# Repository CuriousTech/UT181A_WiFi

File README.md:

# UT181A_WiFi
Uni-T UT181A WiFi Interface  

Optically isolated interface for the UT181A using the ESP8266 for WiFi in either STA or AP mode. USB Rechargeable 1 cell LiPo and optional OLED display, which should be disabled for speed.  

The code is complete. There should be more export formats though. There's a basic web interface and binary WebSocket for a Windows software interface.  
[WindowsApp](https://www.curioustech.net/ut181a.html)  

Web page.  Click the white time on top to update the internal clock. The rest should be the same as what's on the DMM. 

File manager.  Click Saves or Records for listings. Click on files to download, and X to delete.

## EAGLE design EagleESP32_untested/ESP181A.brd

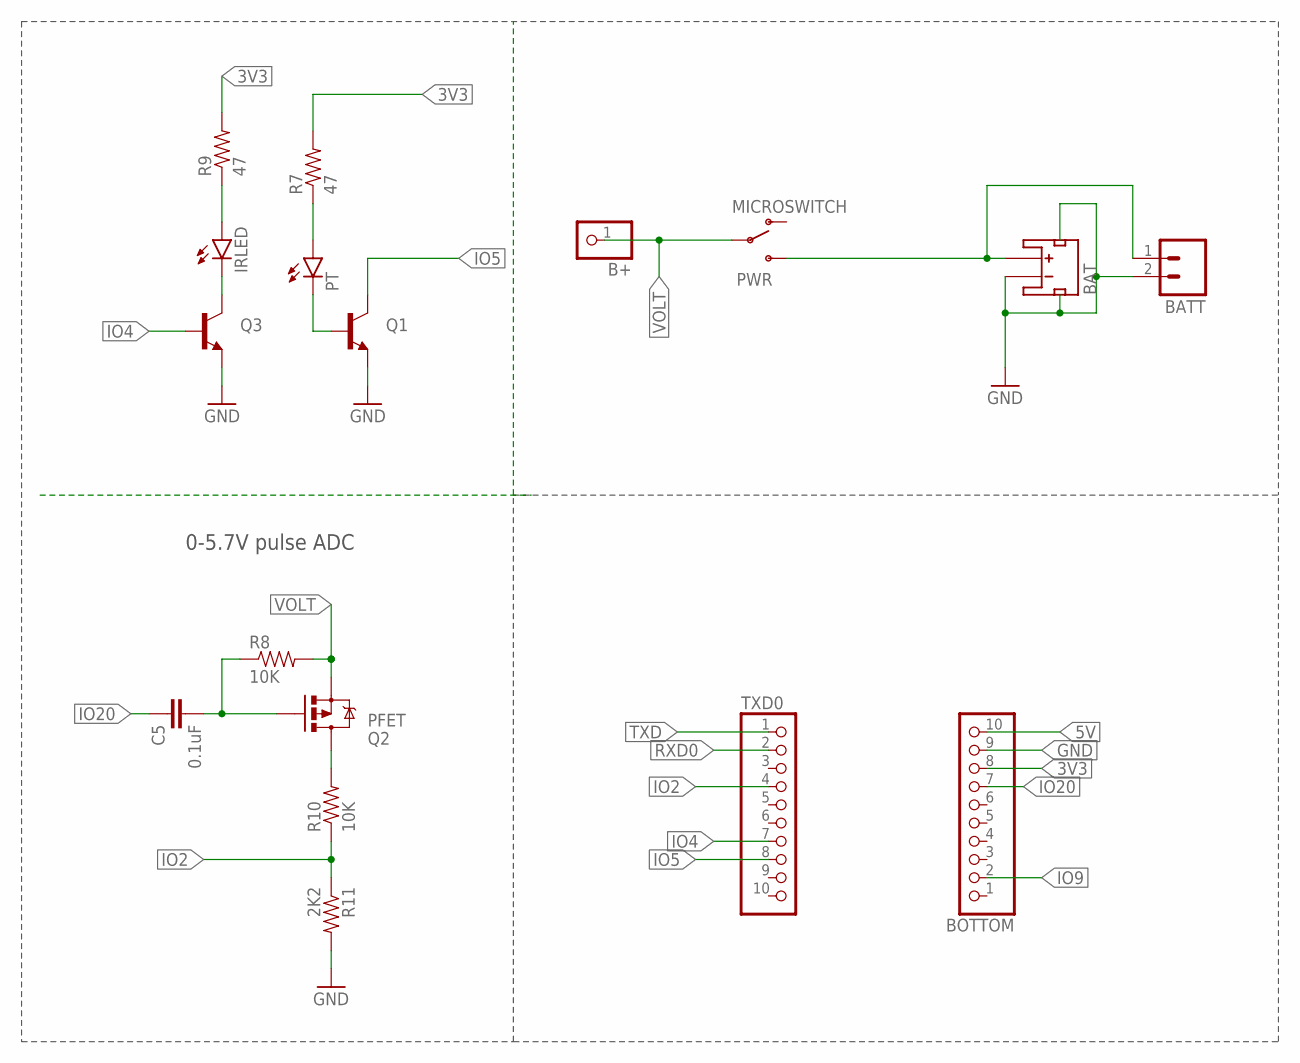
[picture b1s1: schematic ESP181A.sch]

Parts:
B+: PINHD-1X1; 1X01
BAT: JST1.25MM; JST_1.25MM
BATT: M02PTH; 1X02
BOTTOM: PINHD-1X10; 1X10
C5: 0.1uF; 0805-CAP
IRLED: LED3MM
PT: LED3MM
PWR: MICROSWITCH
Q1, Q3: TRANSISTOR_NPNSOT23-3; SOT23-3
Q2: PFET; SOT23-3
R7, R9: 47; 0805
R8, R10: 10K; 0805
R11: 2K2; 0805
TXD0: PINHD-1X10; 1X10

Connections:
3V3: BOTTOM.8, R7.2, R9.2
5V: BOTTOM.10
GND: BAT.1 (-), BAT.NC1 (PAD1), BAT.NC2 (PAD2), BATT.2, BOTTOM.9, Q1.2 (E), Q3.2 (E), R11.2
IO2: R10.1, R11.1, TXD0.4
IO4: Q3.1 (B), TXD0.7
IO5: Q1.3 (C), TXD0.8
IO9: BOTTOM.2
IO20: BOTTOM.7, C5.1
unnamed: IRLED.A, R9.1
unnamed: PT.K (C), Q1.1 (B)
unnamed: BAT.2 (+), BATT.1, PWR.3 (S)
unnamed: PT.A, R7.1
unnamed: C5.2, Q2.1 (G), R8.1
unnamed: Q2.3 (D), R10.2
unnamed: IRLED.K (C), Q3.3 (C)
RXD0: TXD0.2
TXD: TXD0.1
VOLT: B+.1, PWR.2, Q2.2 (S), R8.2

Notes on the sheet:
0-5.7V pulse ADC

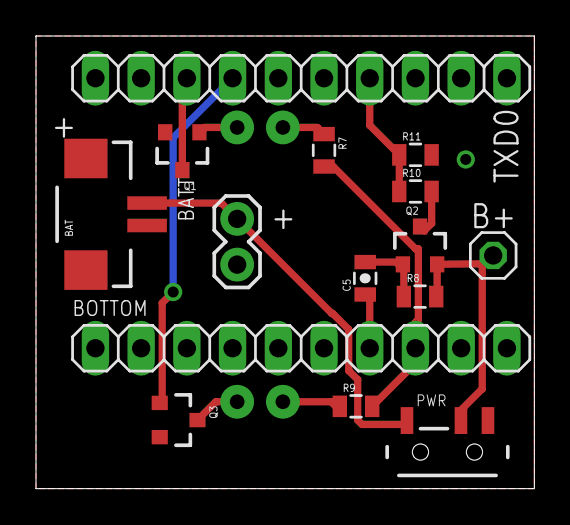
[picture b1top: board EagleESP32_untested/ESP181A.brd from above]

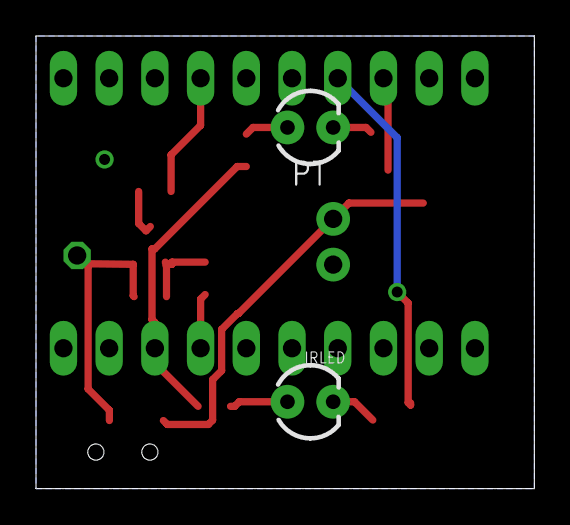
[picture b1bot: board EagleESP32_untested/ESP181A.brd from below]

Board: 2 copper layers, 27.7 x 25.1 mm, 17 parts (2 on the bottom side), 14 nets.

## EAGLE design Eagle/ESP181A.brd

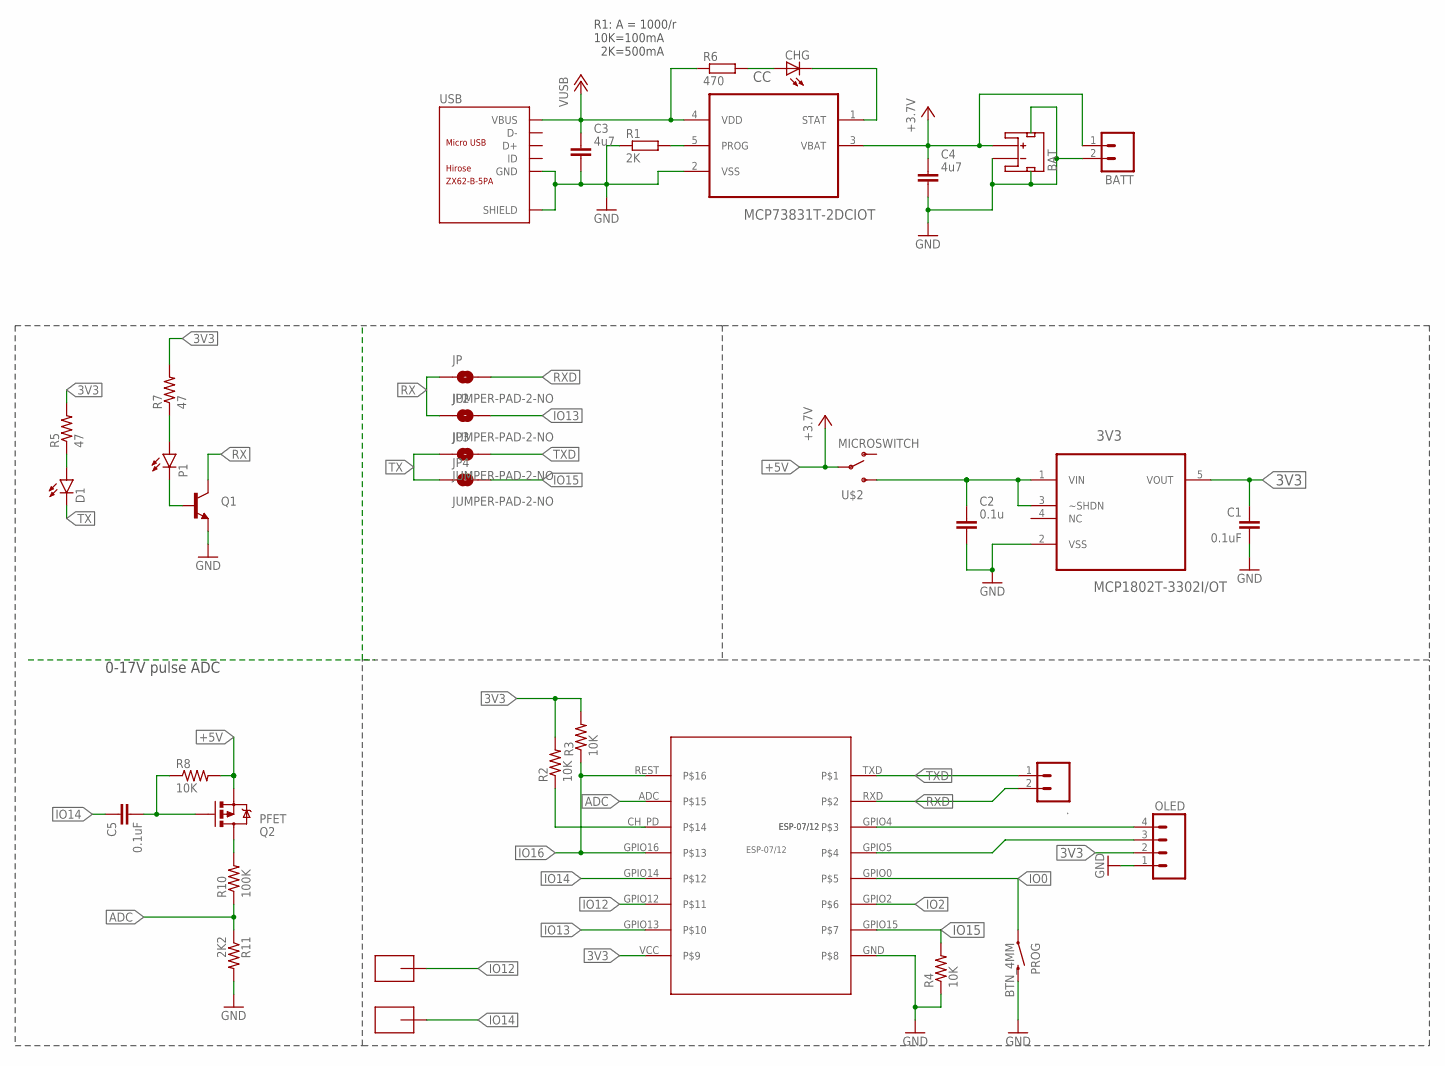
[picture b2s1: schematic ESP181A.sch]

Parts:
3V3: MCP1802T-3302I/OT; SOT95P270X145-5N
.: M02PTH; 1X02
BAT: JST1.25MM; JST_1.25MM
BATT: M02PTH; 1X02
C1, C5: 0.1uF; 0805-CAP
C2: 0.1u; C603
C3, C4: 4u7; C603
CC: MCP73831T-2DCIOT; SOT95P280X145-5N
CHG: LEDCHIP-LED0805; CHIP-LED0805
D1: LED3MM
JP, JP2, JP3, JP4: JUMPER-PAD-2-NO; PAD-JUMPER-2-NO_NO_SILK
OLED: M04PTH; 1X04
P1: LED3MM
PROG: BTN_4MM
Q1: TRANSISTOR_NPNSOT23-3; SOT23-3
Q2: PFET; SOT23-3
R1: 2K; R603
R2, R3, R4, R8: 10K; 0805
R5, R7: 47; 0805
R6: 470; R603
R10: 100K; 0805
R11: 2K2; 0805
U$1: ESP-07/12
U$2: MICROSWITCH
U$3, U$4: SMD-PAD182X64; SMD-PAD1
USB: ZX62-B-5PA; MICRO-USB5+6P-SMD-0.65-AB

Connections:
3V3: 3V3.5 (VOUT), C1.1, OLED.2, R2.2, R3.2, R5.2, R7.2, U$1.VCC
+5V: BAT.2 (+), BATT.1, C4.1, CC.3 (VBAT), Q2.2 (S), R8.2, U$2.2
ADC: R10.1, R11.1, U$1.ADC
CH_PD: R2.1, U$1.CH_PD
GND: 3V3.2 (VSS), BAT.1 (-), BAT.NC1 (PAD1), BAT.NC2 (PAD2), BATT.2, C1.2, C2.2, C3.2, C4.2, CC.2 (VSS), OLED.1, PROG.2, Q1.2 (E), R1.1, R4.1, R11.2, U$1.GND, USB.5 (GND), USB.P1 (SHIELD), USB.P2 (SHIELD), USB.P3 (SHIELD), USB.P4 (SHIELD), USB.P5 (SHIELD), USB.P6 (SHIELD)
IO0: PROG.1, U$1.GPIO0
IO2: U$1.GPIO2
IO12: U$1.GPIO12, U$4.>PAD
IO13: JP2.2, U$1.GPIO13
IO14: C5.1, U$1.GPIO14, U$3.>PAD
IO15: JP4.2, R4.2, U$1.GPIO15
IO16: R3.1, U$1.GPIO16, U$1.REST
unnamed: D1.A, R5.1
unnamed: P1.K (C), Q1.1 (B)
unnamed: OLED.4, U$1.GPIO4
unnamed: CHG.A, R6.2
unnamed: CC.1 (STAT), CHG.C
unnamed: OLED.3, U$1.GPIO5
unnamed: CC.5 (PROG), R1.2
unnamed: 3V3.1 (VIN), 3V3.3 (~SHDN), C2.1, U$2.3 (S)
unnamed: P1.A, R7.1
unnamed: C5.2, Q2.1 (G), R8.1
unnamed: Q2.3 (D), R10.2
RX: JP.1, JP2.1, Q1.3 (C)
RXD: ..2, JP.2, U$1.RXD
TX: D1.K (C), JP3.1, JP4.1
TXD: ..1, JP3.2, U$1.TXD
VBUS: C3.1, CC.4 (VDD), R6.1, USB.1 (VBUS)

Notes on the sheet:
R1: A = 1000/r 10K=100mA 2K=500mA
0-17V pulse ADC

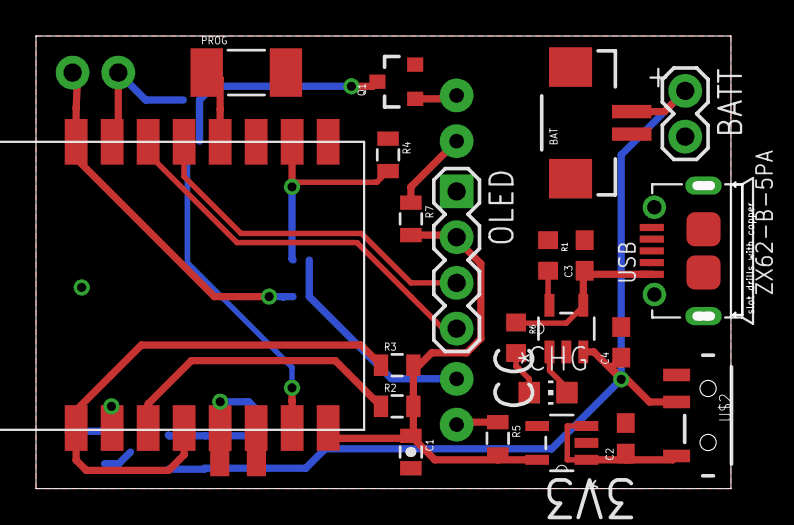
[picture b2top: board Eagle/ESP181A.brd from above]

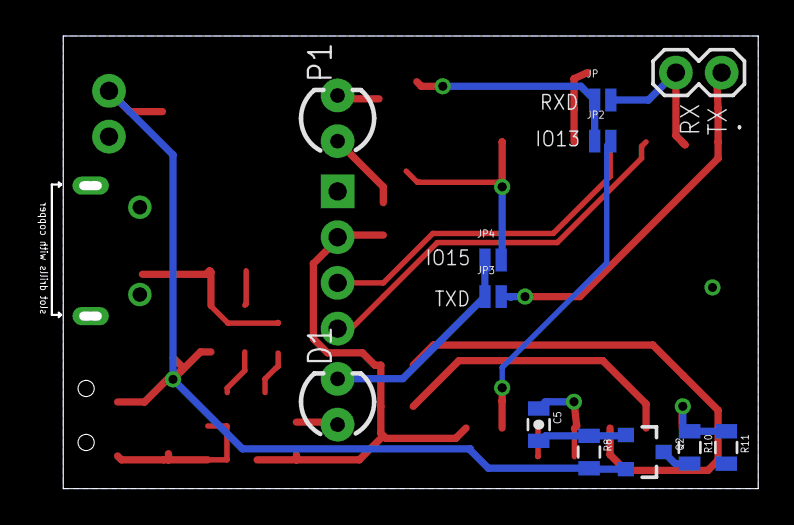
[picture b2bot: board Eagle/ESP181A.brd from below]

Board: 2 copper layers, 39.6 x 24.6 mm, 36 parts (12 on the bottom side), 27 nets.

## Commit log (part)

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2018-09-15 Still incomplete
2018-09-15 More additions
2018-09-15 Cleanup, additions
2018-09-15 Cleanup
2018-09-15 Added file listings
2018-09-15 Changes to reflect server files
2018-09-15 File server additions
2018-09-15 File server/list additions
2018-09-17 Additions for file download
2018-09-19 many fixes
2018-09-19 File download fixes
2018-09-19 Added file delete
2018-09-19 Added battery voltage monitor
2018-09-20 Fixed bar hide
2018-09-23 Set clock and sel
2018-09-23 Labels, set select
2018-09-23 Add last clock update stamp
2018-09-23 Changed value types multi line chart
2018-09-25 More cleanup
2018-09-25 Moved record popup
2018-09-25 temperature label fixes
2018-10-04 Expanded bit flags
2018-10-04 Changed code for flags
2018-10-04 Fixed 10Hz bar update
2018-10-04 Conversion for flags
2018-10-04 Added OLED hole
2018-10-15 Reverted a few bits
2018-10-15 Reverted some bits
2018-10-15 Batt voltage, centered items
2018-10-15 Batt voltage, reverted bits
2018-10-16 unmatched quote removed
2018-10-16 fixed some unit labels
2018-11-12 Cap discharge bit added
2018-11-12 Cleaned up
2018-11-12 Changed flags to hex, batt update when not connected
2018-11-14 refresh
2018-11-14 more compact data
2018-11-14 Compact data and clock set
2019-04-13 fix for 2.5.0 and bug
2020-05-08 Mousewheel zoom
2020-05-08 Changed error msgs
2020-05-08 Reset string
2020-05-08 Commented out ISR
2020-05-08 Graph zoom and slide
2020-05-10 Typo: sclk
2020-05-10 Typo in zoom
2022-01-03 Using rawliteral
2022-01-03 Async wifi manager
2022-01-03 Changes for the async wifi manager
2022-01-03 Forgot to update this
2022-01-03 Forgot to update
2023-01-27 C++17 compliant
2023-01-27 AP/STA mode
2023-01-27 Struct merge
2023-01-27 C++17
2023-02-03 Changes for simpler json
2023-02-03 json changes
2024-04-15 bug in zoom

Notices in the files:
parts and their libraries:
SparkFun-Connectors: Licensing: Creative Commons ShareAlike 4.0 International - https://creativecommons.org/licenses/by-sa/4.0
